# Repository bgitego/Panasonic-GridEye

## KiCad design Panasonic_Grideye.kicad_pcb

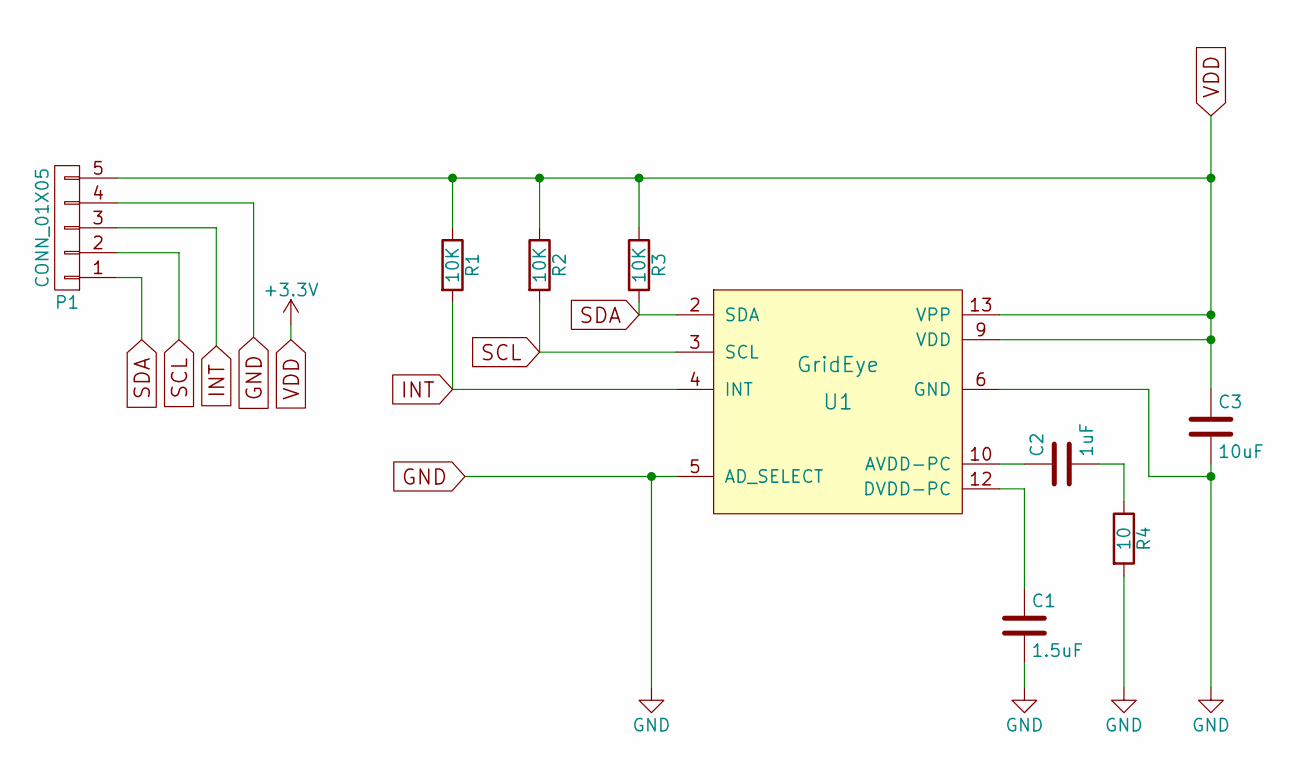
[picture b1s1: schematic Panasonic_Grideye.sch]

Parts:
C1: 1.5uF; C_0805_HandSoldering
C2: 1uF; C_0805_HandSoldering
C3: 10uF; C_0805_HandSoldering
P1: CONN_01X05; Pin_Header_Straight_1x05_Pitch2.54mm
R1, R2, R3: 10K; R_0805_HandSoldering
R4: 10; R_0805_HandSoldering
U1: GridEye; AMG8851

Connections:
GND: C1.2, C3.2, P1.4, R4.2, U1.5 (AD_SELECT), U1.6 (GND)
INT: P1.3, R1.2, U1.4 (INT)
unnamed: C1.1, U1.12 (DVDD-PC)
unnamed: C2.1, U1.10 (AVDD-PC)
unnamed: C2.2, R4.1
SCL: P1.2, R2.2, U1.3 (SCL)
SDA: P1.1, R3.2, U1.2 (SDA)
VDD: C3.1, P1.5, R1.1, R2.1, R3.1, U1.9 (VDD), U1.13 (VPP)

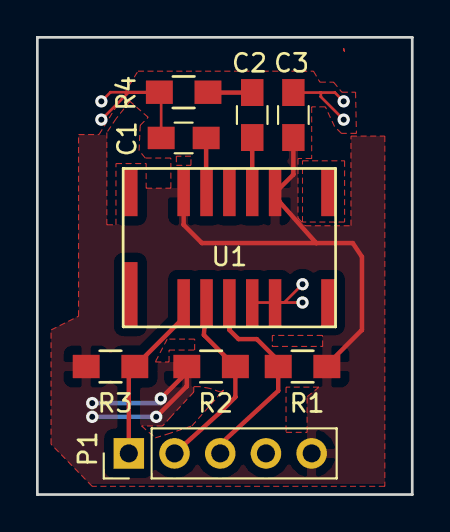
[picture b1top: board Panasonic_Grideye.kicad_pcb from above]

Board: 2 copper layers, 20.8 x 25.4 mm, 9 parts (0 on the bottom side), 8 nets.

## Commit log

2017-02-06 Adding Panasonic GridEye Thermal Grid Array Revision 1
2017-06-22 Adding Revesion To The Board
2017-06-22 Updating Changes Made to Board Files
